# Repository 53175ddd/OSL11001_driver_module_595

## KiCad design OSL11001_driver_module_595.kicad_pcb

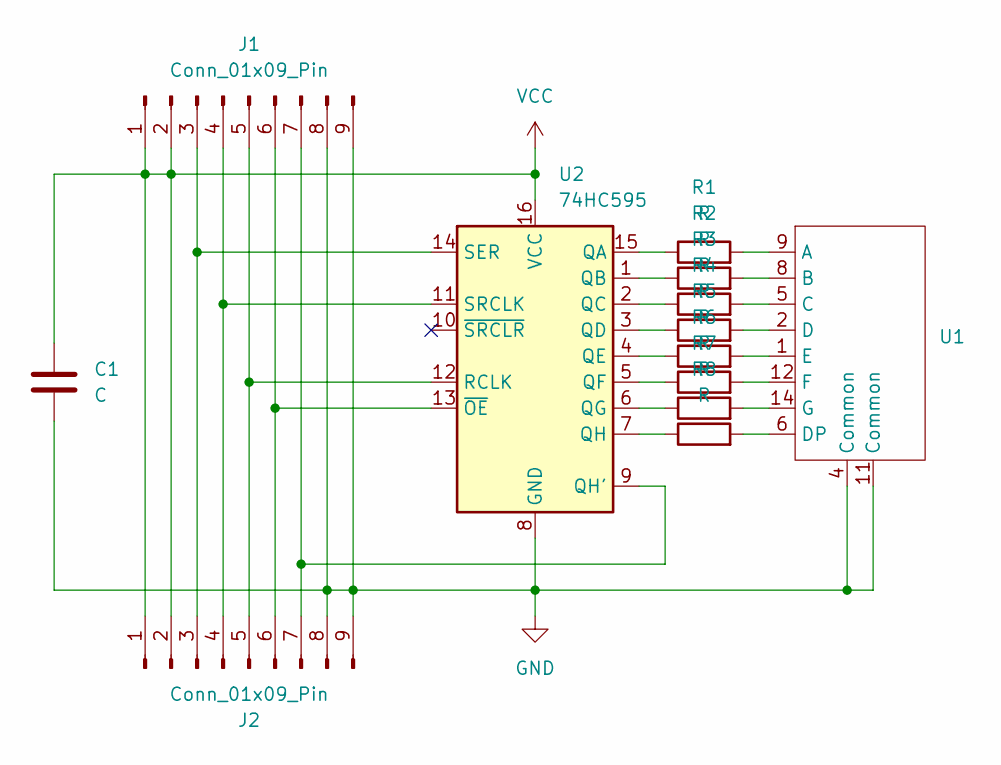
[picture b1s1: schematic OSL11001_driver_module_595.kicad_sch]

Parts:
C1: C; C_0603_1608Metric; LCSC C1590
J1, J2: Conn_01x09_Pin; PinHeader_1x09_P2.54mm_Vertical
R1, R2, R3, R4, R5, R6, R7: R; R_0603_1608Metric; LCSC C114669
R8: R; R_0603_1608Metric; LCSC C2889411
U1: OSL11001
U2: 74HC595; SOP-16_4.4x10.4mm_P1.27mm; LCSC C18164493

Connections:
GND: C1.2, J1.8, J1.9, J2.8, J2.9, U1.4 (Common), U1.11 (Common), U2.8 (GND)
unnamed: J1.3, J2.3, U2.14 (SER)
unnamed: J1.4, J2.4, U2.11 (SRCLK)
unnamed: J1.5, J2.5, U2.12 (RCLK)
unnamed: J1.6, J2.6, U2.13 (~OE)
unnamed: J1.7, J2.7, U2.9 (QH')
unnamed: R1.2, U1.9 (A)
unnamed: R2.2, U1.8 (B)
unnamed: R3.2, U1.5 (C)
unnamed: R4.2, U1.2 (D)
unnamed: R8.2, U1.6 (DP)
unnamed: R5.2, U1.1 (E)
unnamed: R6.2, U1.12 (F)
unnamed: R7.2, U1.14 (G)
unnamed: R1.1, U2.15 (QA)
unnamed: R2.1, U2.1 (QB)
unnamed: R3.1, U2.2 (QC)
unnamed: R4.1, U2.3 (QD)
unnamed: R5.1, U2.4 (QE)
unnamed: R6.1, U2.5 (QF)
unnamed: R7.1, U2.6 (QG)
unnamed: R8.1, U2.7 (QH)
VCC: C1.1, J1.1, J1.2, J2.1, J2.2, U2.16 (VCC)

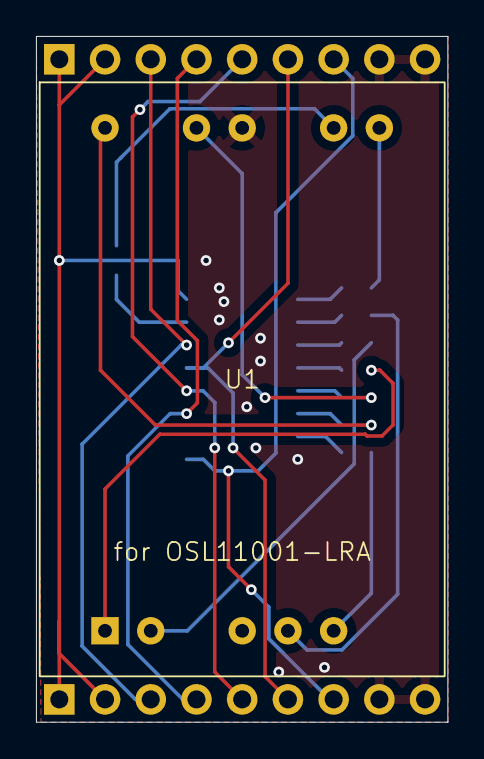
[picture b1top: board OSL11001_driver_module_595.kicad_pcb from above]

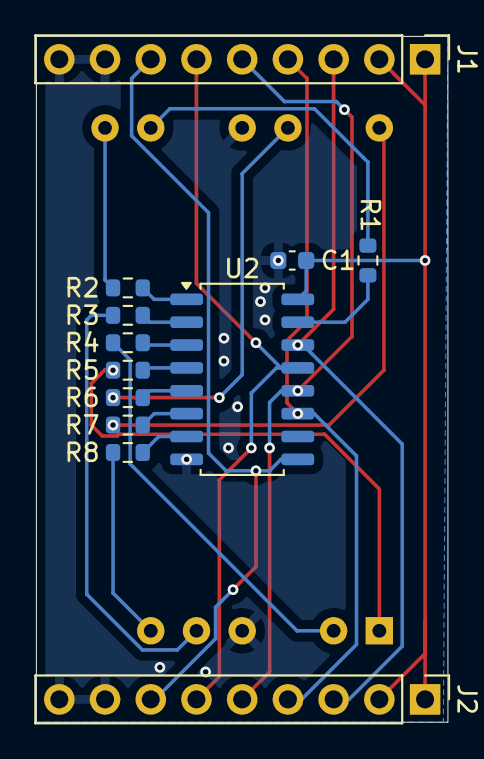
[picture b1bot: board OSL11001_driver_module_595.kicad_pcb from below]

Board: 2 copper layers, 22.9 x 38.1 mm, 13 parts (12 on the bottom side), 23 nets.
